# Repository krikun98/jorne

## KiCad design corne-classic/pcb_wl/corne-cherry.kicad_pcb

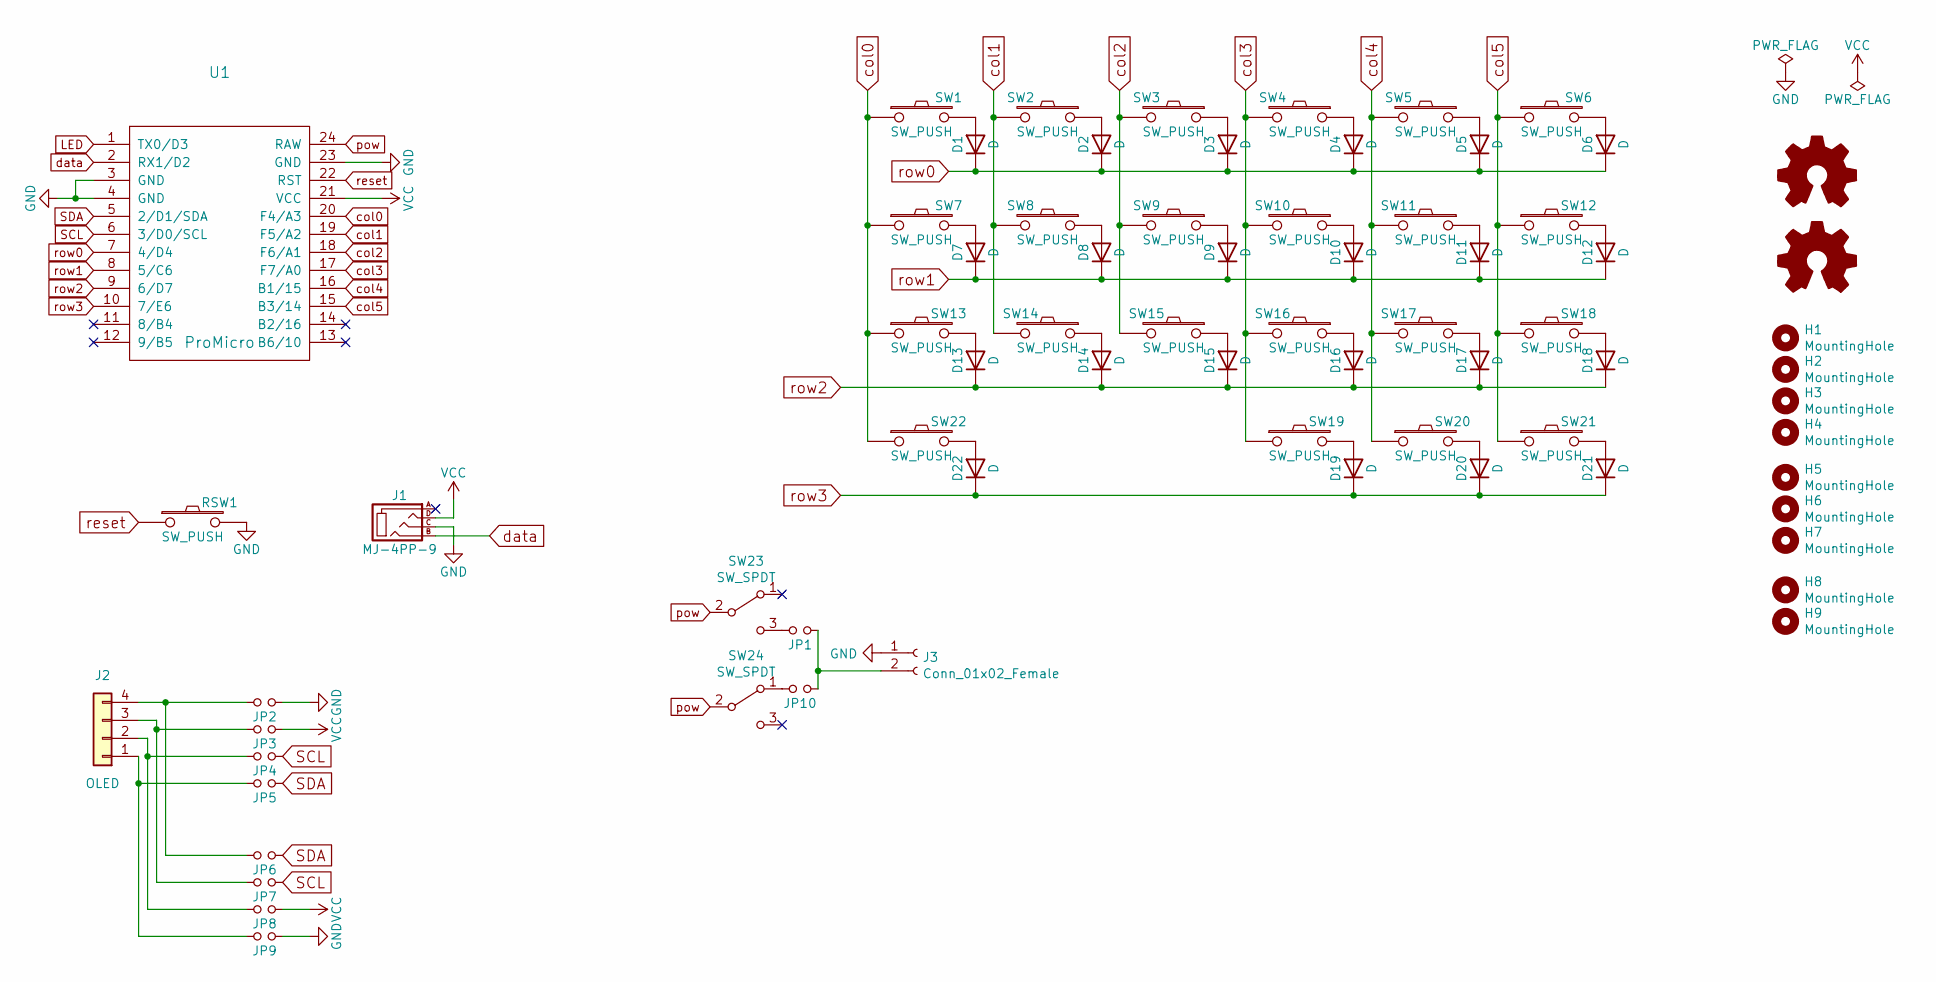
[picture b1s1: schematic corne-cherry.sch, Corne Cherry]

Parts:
D1, D2, D3, D4, D5, D6, D7, D8, D9, D10, D11, D12, D13, D14, D15, D16, D17, D18, D19, D20, D21, D22: D; D3_SMD
G1, G2: Logo_Open_Hardware_Small; sporne-logo-small
H1, H2, H3, H4, H5, H6, H7, H8, H9: MountingHole; LEGO_HOLE
J1: MJ-4PP-9
J2: OLED
J3: Conn_01x02_Female; Battery_Header
JP1, JP2, JP3, JP4, JP5, JP6, JP7, JP8, JP9, JP10: Jumper
RSW1: SW_PUSH; ResetSW
SW1, SW2, SW3, SW4, SW5, SW6, SW7, SW8, SW9, SW10, SW11, SW12, SW13, SW14, SW15, SW16, SW17, SW18, SW22: SW_PUSH; MX_Alps_Hitek_725_1U_reversible
SW19, SW20: SW_PUSH; MX_Alps_Hitek_725_1U_reversible_thumb
SW21: SW_PUSH; MX_Alps_Hitek_725_1.5U_reversible_thumb
SW23, SW24: SW_SPDT; SW_SPDT+H-MSK12C01_hor(7pin_SMD)
U1: ProMicro; ProMicro_v2

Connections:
GND: J1.C, J3.1, JP2.1, JP9.1, RSW1.2, U1.3 (GND), U1.4 (GND), U1.23 (GND)
LED: U1.1 (TX0/D3)
unnamed: D1.2 (A), SW1.2
unnamed: D2.2 (A), SW2.1
unnamed: D3.2 (A), SW3.1
unnamed: D4.2 (A), SW4.1
unnamed: D5.2 (A), SW5.1
unnamed: D6.2 (A), SW6.2
unnamed: D7.2 (A), SW7.2
unnamed: D8.2 (A), SW8.1
unnamed: D9.2 (A), SW9.1
unnamed: D10.2 (A), SW10.1
unnamed: D11.2 (A), SW11.1
unnamed: D12.2 (A), SW12.2
unnamed: D13.2 (A), SW13.2
unnamed: D14.2 (A), SW14.1
unnamed: D15.2 (A), SW15.1
unnamed: D16.2 (A), SW16.1
unnamed: D17.2 (A), SW17.1
unnamed: D18.2 (A), SW18.2
unnamed: D19.2 (A), SW19.2
unnamed: D20.2 (A), SW20.2
unnamed: D21.2 (A), SW21.2
unnamed: D22.2 (A), SW22.2
unnamed: J2.1, JP5.2, JP9.2
unnamed: J2.2, JP4.2, JP8.2
unnamed: J2.3, JP3.2, JP7.2
unnamed: J2.4, JP2.2, JP6.2
unnamed: J3.2, JP1.1, JP10.1
unnamed: JP1.2, SW23.3 (C)
unnamed: JP10.2, SW24.1 (A)
SCL: JP4.1, JP7.1, U1.6 (3/D0/SCL)
SDA: JP5.1, JP6.1, U1.5 (2/D1/SDA)
VCC: J1.D, JP3.1, JP8.1, U1.21 (VCC)
col0: SW1.1, SW7.1, SW13.1, SW22.1, U1.20 (F4/A3)
col1: SW2.2, SW8.2, SW14.2, U1.19 (F5/A2)
col2: SW3.2, SW9.2, SW15.2, U1.18 (F6/A1)
col3: SW4.2, SW10.2, SW16.2, SW19.1, U1.17 (F7/A0)
col4: SW5.2, SW11.2, SW17.2, SW20.1, U1.16 (B1/15)
col5: SW6.1, SW12.1, SW18.1, SW21.1, U1.15 (B3/14)
data: J1.B, U1.2 (RX1/D2)
pow: SW23.2 (B), SW24.2 (B), U1.24 (RAW)
reset: RSW1.1, U1.22 (RST)
row0: D1.1 (K), D2.1 (K), D3.1 (K), D4.1 (K), D5.1 (K), D6.1 (K), U1.7 (4/D4)
row1: D7.1 (K), D8.1 (K), D9.1 (K), D10.1 (K), D11.1 (K), D12.1 (K), U1.8 (5/C6)
row2: D13.1 (K), D14.1 (K), D15.1 (K), D16.1 (K), D17.1 (K), D18.1 (K), U1.9 (6/D7)
row3: D19.1 (K), D20.1 (K), D21.1 (K), D22.1 (K), U1.10 (7/E6)

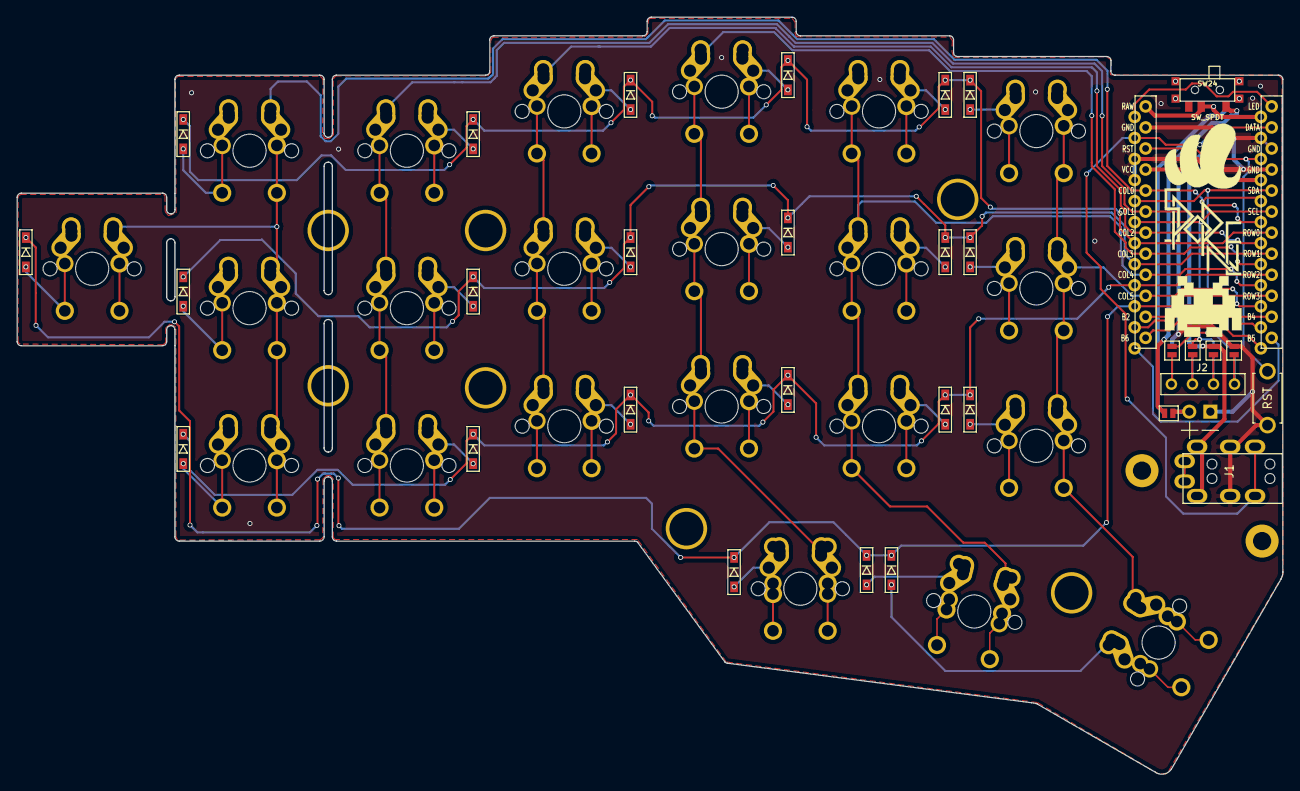
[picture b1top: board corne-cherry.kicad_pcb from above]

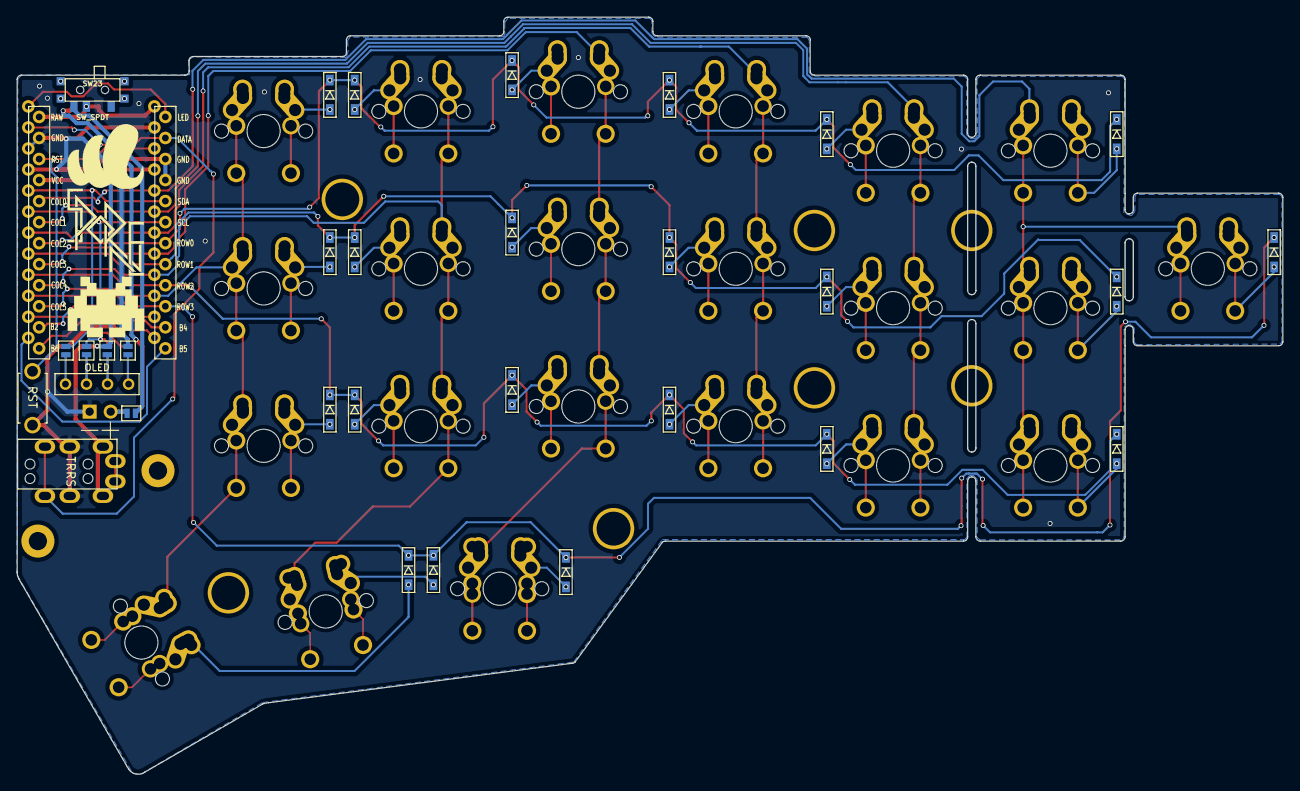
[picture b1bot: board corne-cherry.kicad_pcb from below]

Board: 2 copper layers, 152.8 x 91.4 mm, 72 parts (7 on the bottom side), 46 nets.

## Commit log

2021-07-20 Reversible MX/Hi-Tek 725 wireless PCB
2021-07-21 Improver SI footprint, ground fills
2021-07-21 Added power switch stabilization vias
2021-07-24 flipped footprints
2021-08-13 Added proper SPORNE logo
2021-08-13 Added gerbers
2021-08-29 Logo fix
2021-10-01 Diode via fix
2021-10-03 Bigger battery header, cleaner switch footprints and schematic
2021-10-03 Moved to classic folder
2021-10-03 Fixed reset text
2021-12-02 Added Alps support and invertible SI thumbs
2021-12-02 Added SI plates
2021-12-02 Added custom footprints for SI
2021-12-02 Added plate DXF
2021-12-02 Minor fixes, updated gerbers
2021-12-02 Added Alps plate
2021-12-02 Added images, gerbers and DXF files
2021-12-06 Fixed screw hole sizes
